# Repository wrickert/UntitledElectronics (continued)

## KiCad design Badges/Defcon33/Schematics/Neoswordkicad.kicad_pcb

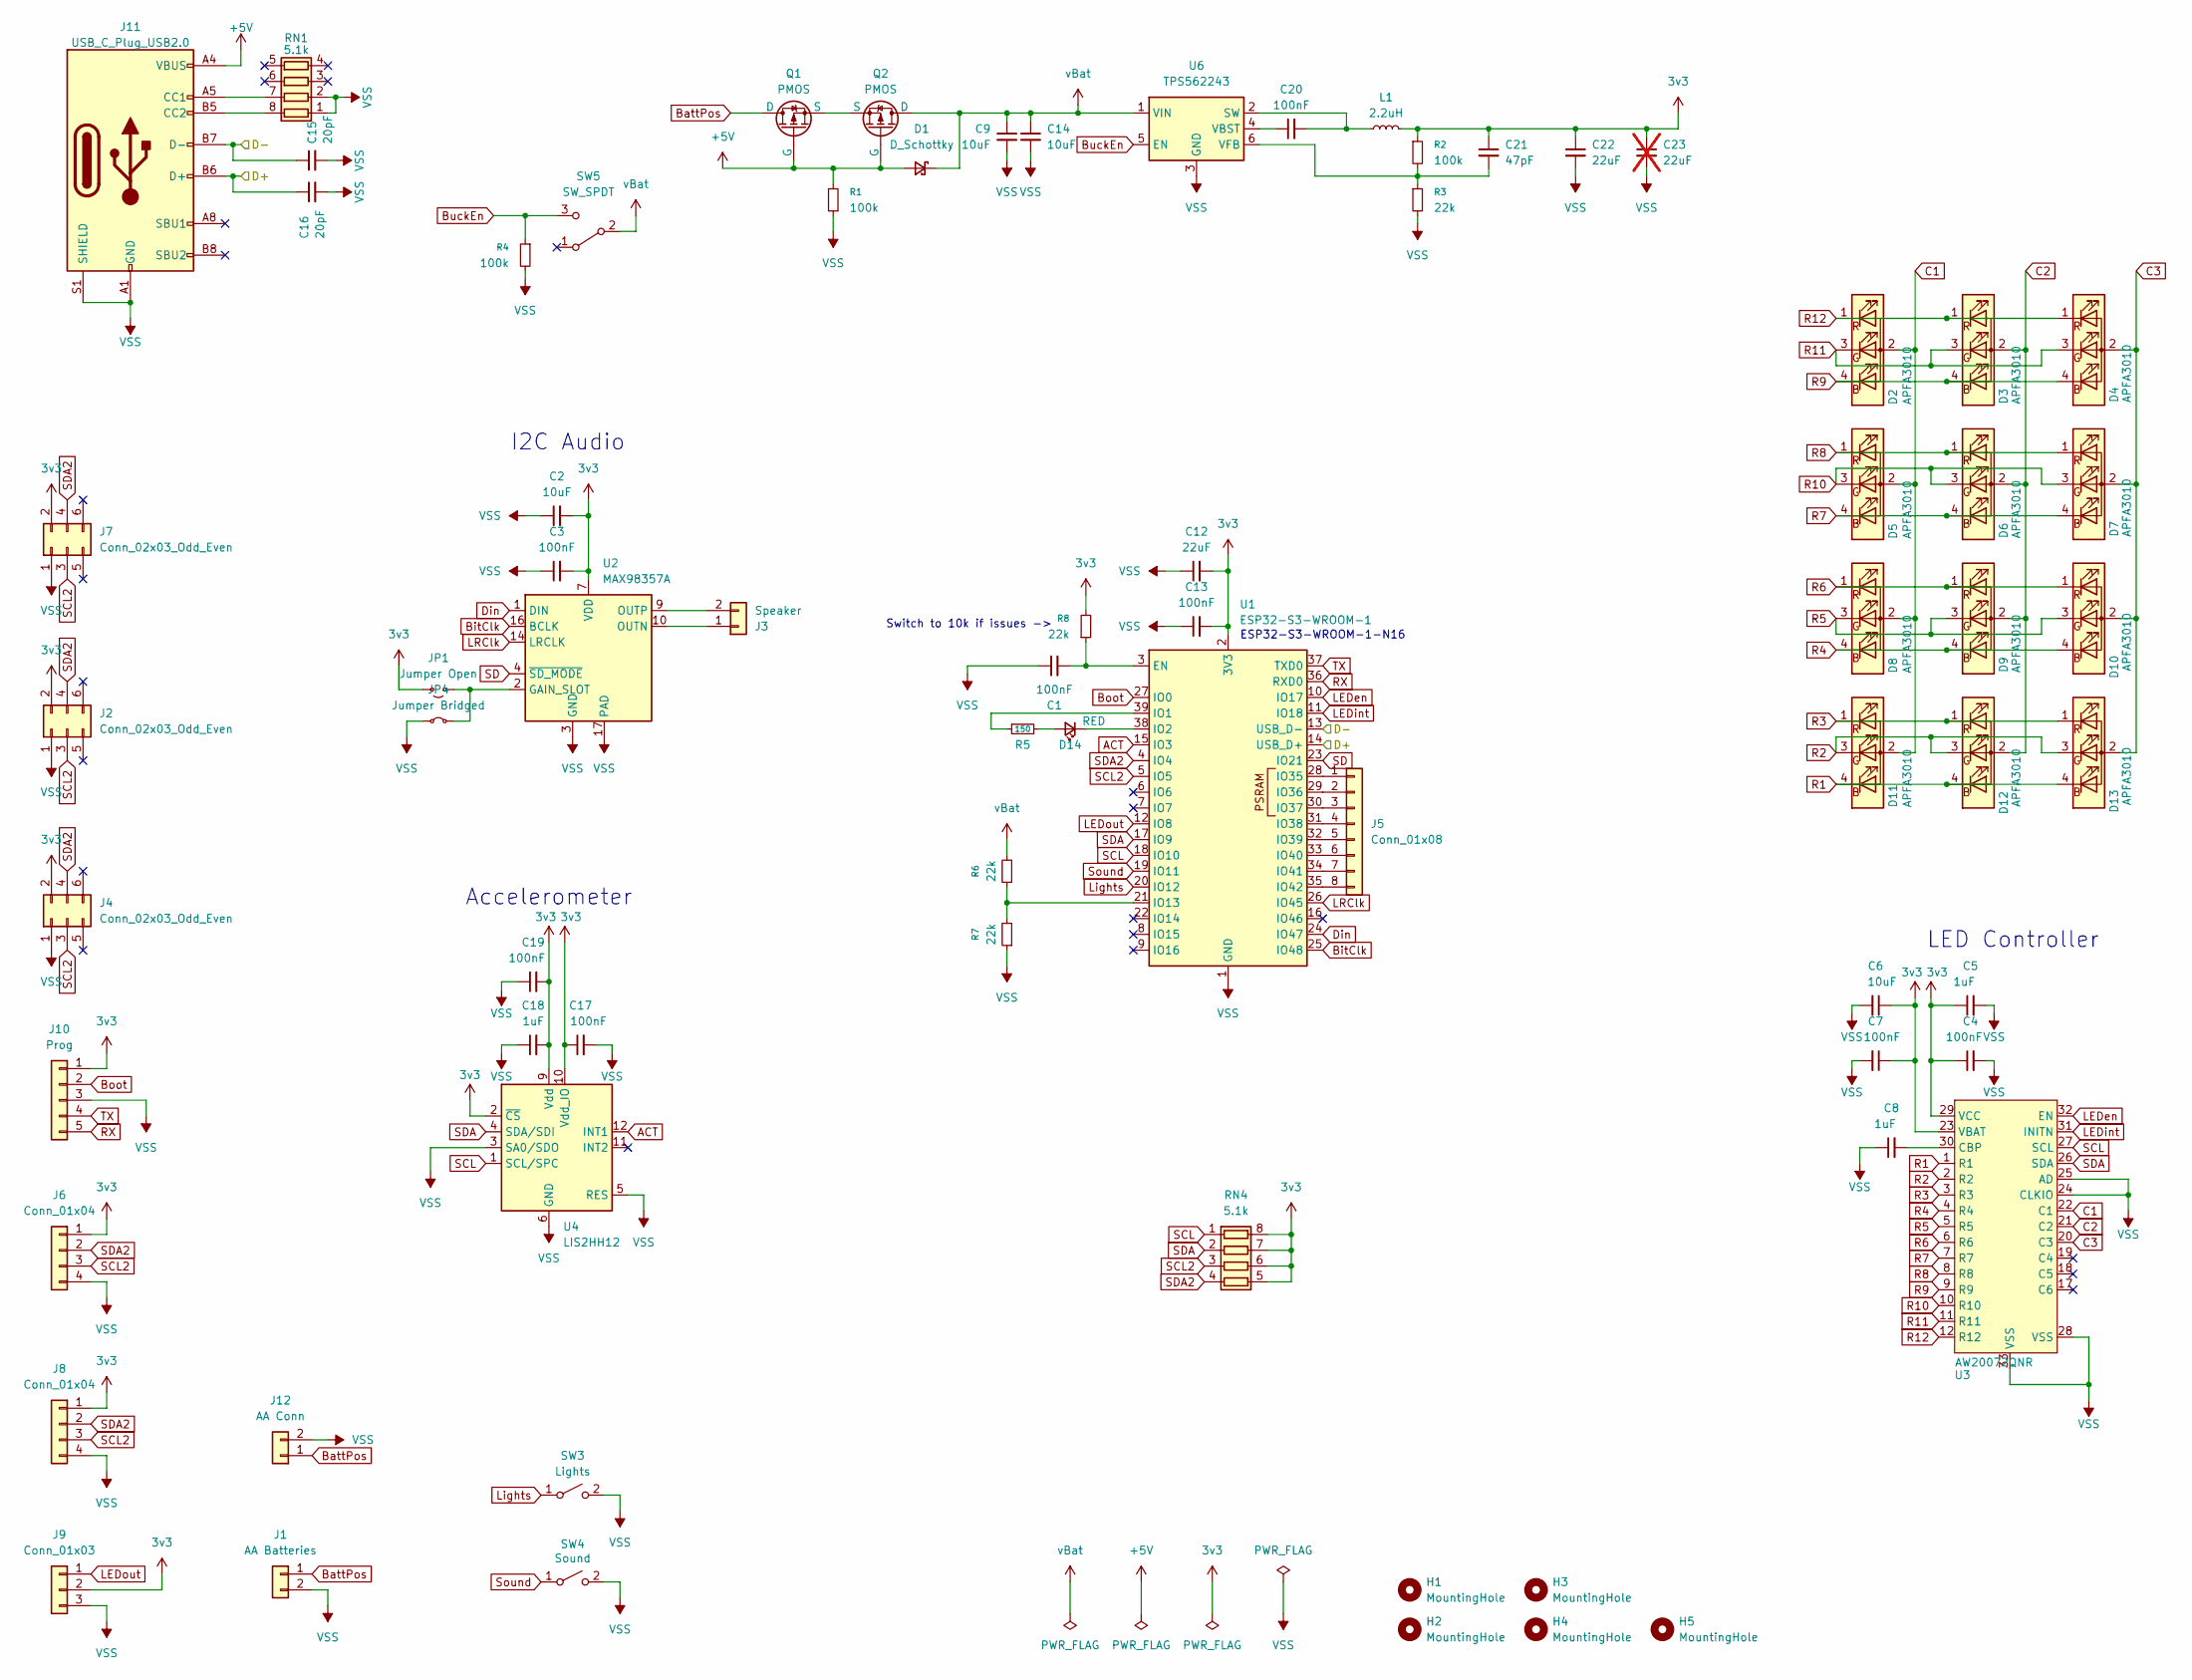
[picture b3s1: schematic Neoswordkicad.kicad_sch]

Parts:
C1, C3, C4, C7, C13, C17, C19, C20: 100nF; C_0805_2012Metric
C2, C6, C9, C14: 10uF; C_0805_2012Metric
C5, C8, C18: 1uF; C_0805_2012Metric
C12, C22: 22uF; C_0805_2012Metric
C15, C16: 20pF; C_0805_2012Metric
C21: 47pF; C_0805_2012Metric
C23: 22uF; C_0805_2012Metric; not fitted
D1: D_Schottky; D_0805_2012Metric
D2, D3, D4, D5, D6, D7, D8, D9, D10, D11, D12, D13: APFA3010; FM-3510RGBA-SG_RGB
D14: RED
H1, H2: MountingHole; MountingHole_3.2mm_M3_DIN965_Pad
H3: MountingHole; MountingHole_3.2mm_M3
H4, H5: MountingHole; Threaded_Standoffs
J1: AA Batteries; 1016_2AA
J2, J4, J7: Conn_02x03_Odd_Even; PinHeader_2x03_P2.54mm_Vertical
J3: Speaker; Molex_PicoBlade_53261-0271_1x02-1MP_P1.25mm_Horizontal
J5: Conn_01x08; PinHeader_1x08_P1.00mm_Vertical
J6, J8: Conn_01x04; Molex_PicoBlade_53261-0471_1x04-1MP_P1.25mm_Horizontal
J9: Conn_01x03; PinHeader_1x03_P2.54mm_Vertical
J10: Prog; PinHeader_1x05_P2.54mm_Vertical
J11: USB_C_Plug_USB2.0; USB_C_Receptical-Jing
J12: AA Conn; Molex_PicoBlade_53261-0271_1x02-1MP_P1.25mm_Horizontal
JP1: Jumper Open; SolderJumper-2_P1.3mm_Open_TrianglePad1.0x1.5mm
JP4: Jumper Bridged; SolderJumper-2_P1.3mm_Bridged_RoundedPad1.0x1.5mm
L1: 2.2uH; L_Vishay_IFSC-1515AH_4x4x1.8mm
Q1, Q2: PMOS; SOT-23
R1, R2, R4: 100k; R_0805_2012Metric
R3, R6, R7, R8: 22k; R_0805_2012Metric
R5: 150; R_0805_2012Metric
RN1, RN4: 5.1k; R_Array_Convex_4x0603
SW3: Lights; TS3315A
SW4: Sound; TS3315A
SW5: SW_SPDT; SK-3296S_switch
U1: ESP32-S3-WROOM-1
U2: MAX98357A; TQFN-16-1EP_3x3mm_P0.5mm_EP1.23x1.23mm
U3: AW20072QNR; QFN-32-1EP_4x4mm_P0.4mm_EP2.9x2.9mm
U4: LIS2HH12; LGA-12_2x2mm_P0.5mm
U6: TPS562243; SOT-563

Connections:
3v3: C2.2, C3.2, C4.1, C5.1, C6.1, C7.1, C12.2, C13.2, C17.1, C18.2, C19.2, C21.1, C22.1, C23.1, J2.2, J4.2, J6.1, J7.2, J8.1, J9.2, J10.1, JP1.2 (B), L1.2, R2.1, R8.2, RN4.5 (R4.2), RN4.6 (R3.2), RN4.7 (R2.2), RN4.8 (R1.2), U1.2 (3V3), U2.7 (VDD), U2.8 (VDD), U3.13 (VBAT), U3.23 (VBAT), U3.29 (VCC), U4.2 (~CS), U4.9 (Vdd), U4.10 (Vdd_IO)
+5V: D1.2 (A), J11.A4 (VBUS), J11.A9 (VBUS), J11.B4 (VBUS), J11.B9 (VBUS), Q1.1 (G), Q2.1 (G), R1.1
/D+: C16.1, J11.A6 (D+), J11.B6 (D+), U1.14 (USB_D+)
/D-: C15.1, J11.A7 (D-), J11.B7 (D-), U1.13 (USB_D-)
ACT: U1.15 (IO3), U4.12 (INT1)
BattPos: J1.1, J12.1, Q1.3 (D)
BitClk: U1.25 (IO48), U2.16 (BCLK)
Boot: J10.2, U1.27 (IO0)
BuckEn: R4.1, SW5.3 (C), U6.5 (EN)
C1: D2.2 (A), D5.2 (A), D8.2 (A), D11.2 (A), U3.22 (C1)
C2: D3.2 (A), D6.2 (A), D9.2 (A), D12.2 (A), U3.21 (C2)
C3: D4.2 (A), D7.2 (A), D10.2 (A), D13.2 (A), U3.20 (C3)
Din: U1.24 (IO47), U2.1 (DIN)
LEDen: U1.10 (IO17), U3.32 (EN)
LEDint: U1.11 (IO18), U3.31 (INITN)
LEDout: J9.1, U1.12 (IO8)
LRClk: U1.26 (IO45), U2.14 (LRCLK)
Lights: SW3.1 (A), U1.20 (IO12)
unnamed: D14.2 (A), R5.2
unnamed: D14.1 (K), U1.38 (IO2)
unnamed: J3.1, U2.10 (OUTN)
unnamed: J3.2, U2.9 (OUTP)
unnamed: J5.1, U1.28 (IO35)
unnamed: J5.2, U1.29 (IO36)
unnamed: J5.3, U1.30 (IO37)
unnamed: J5.4, U1.31 (IO38)
unnamed: J5.5, U1.32 (IO39)
unnamed: J5.6, U1.33 (IO40)
unnamed: J5.7, U1.34 (IO41)
unnamed: J5.8, U1.35 (IO42)
unnamed: J11.A5 (CC1), RN1.7 (R2.2)
unnamed: J11.B5 (CC2), RN1.8 (R1.2)
unnamed: JP1.1 (A), JP4.2 (B), U2.2 (GAIN_SLOT)
unnamed: Q1.2 (S), Q2.2 (S)
unnamed: C1.2, R8.1, U1.3 (EN)
unnamed: R5.1, U1.39 (IO1)
unnamed: R6.1, R7.2, U1.21 (IO13)
unnamed: C8.2, U3.30 (CBP)
unnamed: C20.2, L1.1, U6.2 (SW)
unnamed: C20.1, U6.4 (VBST)
unnamed: C21.2, R2.2, R3.1, U6.6 (VFB)
R1: D11.4 (B), D12.4 (B), D13.4 (B), U3.1 (R1)
R2: D11.3 (G), D12.3 (G), D13.3 (G), U3.2 (R2)
R3: D11.1 (R), D12.1 (R), D13.1 (R), U3.3 (R3)
R4: D8.4 (B), D9.4 (B), D10.4 (B), U3.4 (R4)
R5: D8.3 (G), D9.3 (G), D10.3 (G), U3.5 (R5)
R6: D8.1 (R), D9.1 (R), D10.1 (R), U3.6 (R6)
R7: D5.4 (B), D6.4 (B), D7.4 (B), U3.7 (R7)
R8: D5.1 (R), D6.1 (R), D7.1 (R), U3.8 (R8)
R9: D2.4 (B), D3.4 (B), D4.4 (B), U3.9 (R9)
R10: D5.3 (G), D6.3 (G), D7.3 (G), U3.10 (R10)
R11: D2.3 (G), D3.3 (G), D4.3 (G), U3.11 (R11)
R12: D2.1 (R), D3.1 (R), D4.1 (R), U3.12 (R12)
RX: J10.5, U1.36 (RXD0)
SCL: RN4.1 (R1.1), U1.18 (IO10), U3.27 (SCL), U4.1 (SCL/SPC)
SCL2: J2.3, J4.3, J6.3, J7.3, J8.3, RN4.3 (R3.1), U1.5 (IO5)
SD: U1.23 (IO21), U2.4 (~SD_MODE)
SDA: RN4.2 (R2.1), U1.17 (IO9), U3.26 (SDA), U4.4 (SDA/SDI)
SDA2: J2.4, J4.4, J6.2, J7.4, J8.2, RN4.4 (R4.1), U1.4 (IO4)
Sound: SW4.1 (A), U1.19 (IO11)
TX: J10.4, U1.37 (TXD0)
VSS: C1.1, C2.1, C3.1, C4.2, C5.2, C6.2, C7.2, C8.1, C9.2, C12.1, C13.1, C14.2, C15.2, C16.2, C17.2, C18.1, C19.1, C22.2, C23.2, J1.2, J2.1, J4.1, J6.4, J7.1, J8.4, J9.3, J10.3, J11.A1 (GND), J11.A12 (GND), J11.B1 (GND), J11.B12 (GND), J11.S1 (SHIELD), J12.2, JP4.1 (A), R1.2, R3.2, R4.2, R7.1, RN1.1 (R1.1), RN1.2 (R2.1), SW3.2 (B), SW4.2 (B), U1.1 (GND), U1.40 (GND), U1.41 (GND), U2.3 (GND), U2.11 (GND), U2.15 (GND), U2.17 (PAD), U3.24 (CLKIO), U3.25 (AD), U3.28 (VSS), U3.33 (VSS), U4.3 (SA0/SDO), U4.5 (RES), U4.6 (GND), U4.7 (GND), U4.8 (GND), U6.3 (GND)
vBat: C9.1, C14.1, D1.1 (K), Q2.3 (D), R6.2, SW5.2 (B), U6.1 (VIN)

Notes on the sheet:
ESP32-S3-WROOM-1-N16
Accelerometer
LED Controller
Switch to 10k if issues ->
I2C Audio

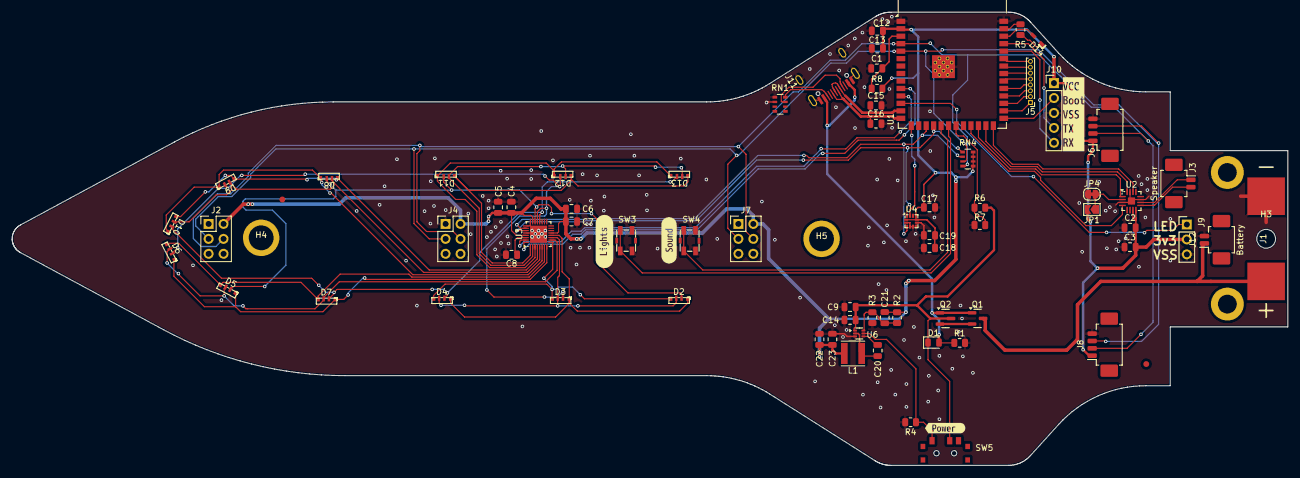
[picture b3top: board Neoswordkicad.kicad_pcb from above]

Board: 2 copper layers, 217.0 x 77.1 mm, 79 parts (0 on the bottom side), 63 nets.

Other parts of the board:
kibuzzard-684F57A2: G***; kibuzzard-684F57A2
kibuzzard-684F57B2: G***; kibuzzard-684F57B2
kibuzzard-684F5906: G***; kibuzzard-684F5906
kibuzzard-6850B9A9: G***; kibuzzard-6850B9A9

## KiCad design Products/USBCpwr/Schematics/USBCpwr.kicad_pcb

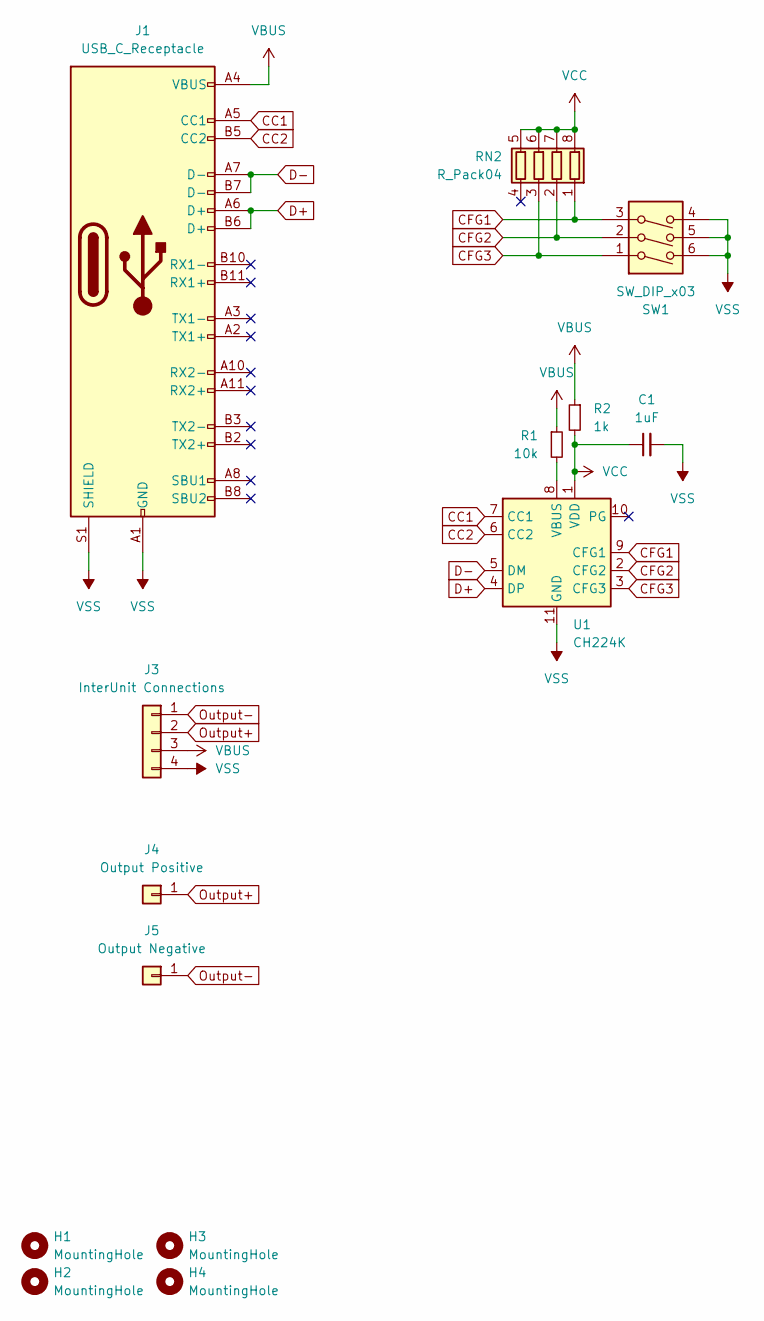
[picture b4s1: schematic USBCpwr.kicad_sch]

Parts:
C1: 1uF; C_0805_2012Metric
H1, H2, H3, H4: MountingHole; MountingHole_2.2mm_M2
J1: USB_C_Receptacle; USB_C_Receptical-Jing
J3: InterUnit Connections; Altech_AK100_1x04_P5.00mm
J4: Output Positive; Banana24_245_1
J5: Output Negative; Banana24_245_1
R1: 10k; R_0805_2012Metric
R2: 1k; R_0805_2012Metric
RN2: R_Pack04; R_Array_Convex_4x0603
SW1: SW_DIP_x03; SW_DIP_SPSTx03_Slide_6.7x9.18mm_W6.73mm_P2.54mm_LowProfile_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
U1: CH224K; SSOP-10-1EP_3.9x4.9mm_P1mm_EP2.1x3.3mm

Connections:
CC1: J1.A5 (CC1), U1.7 (CC1)
CC2: J1.B5 (CC2), U1.6 (CC2)
CFG1: RN2.1 (R1.1), SW1.3, U1.9 (CFG1)
CFG2: RN2.2 (R2.1), SW1.2, U1.2 (CFG2)
CFG3: RN2.3 (R3.1), SW1.1, U1.3 (CFG3)
D+: J1.A6 (D+), J1.B6 (D+), U1.4 (DP)
D-: J1.A7 (D-), J1.B7 (D-), U1.5 (DM)
unnamed: R1.2, U1.8 (VBUS)
Output+: J3.2, J4.1
Output-: J3.1, J5.1
VBUS: J1.A4 (VBUS), J1.A9 (VBUS), J1.B4 (VBUS), J1.B9 (VBUS), J3.3, R1.1, R2.1
VCC: C1.1, R2.2, RN2.5 (R4.2), RN2.6 (R3.2), RN2.7 (R2.2), RN2.8 (R1.2), U1.1 (VDD)
VSS: C1.2, J1.A1 (GND), J1.A12 (GND), J1.B1 (GND), J1.B12 (GND), J1.S1 (SHIELD), J3.4, SW1.4, SW1.5, SW1.6, U1.11 (GND)

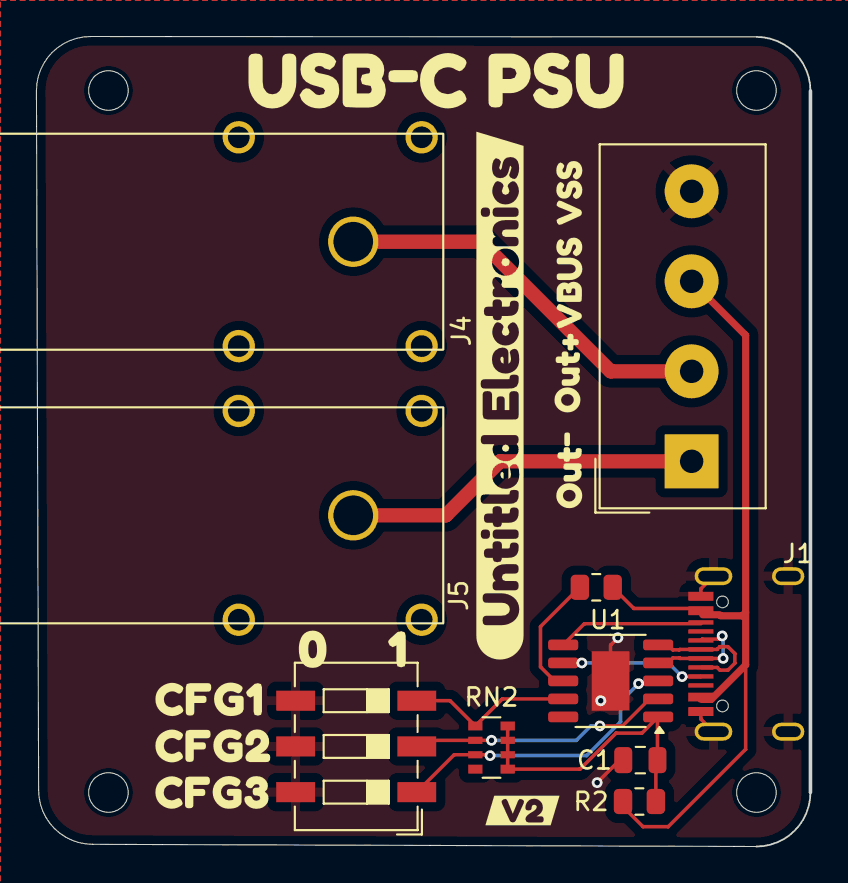
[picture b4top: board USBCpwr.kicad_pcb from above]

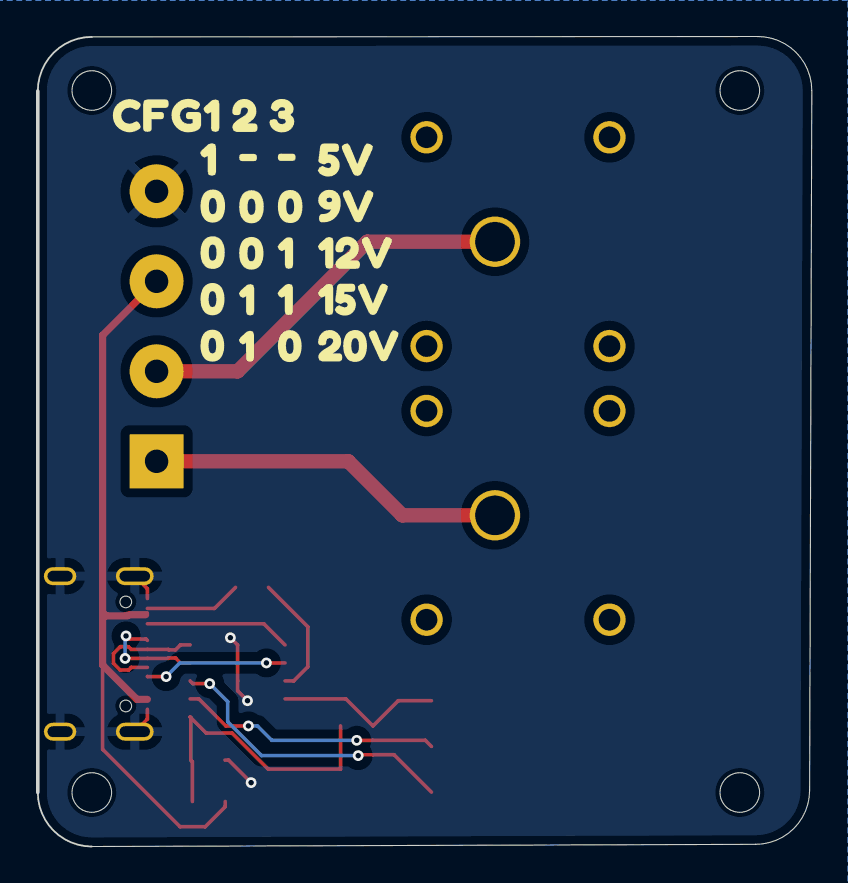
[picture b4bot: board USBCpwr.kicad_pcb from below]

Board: 2 copper layers, 42.9 x 44.9 mm, 28 parts (5 on the bottom side), 13 nets.

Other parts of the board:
kibuzzard-6903A84F: G***; kibuzzard-6903A84F
kibuzzard-67741D43: G***; kibuzzard-67741D43
kibuzzard-67742A98: G***; kibuzzard-67742A98
kibuzzard-67742AAA: G***; kibuzzard-67742AAA
kibuzzard-67742ABC: G***; kibuzzard-67742ABC
kibuzzard-67742BC8: G***; kibuzzard-67742BC8
kibuzzard-67742BCF: G***; kibuzzard-67742BCF
kibuzzard-67742BE6: G***; kibuzzard-67742BE6
kibuzzard-67742BF7: G***; kibuzzard-67742BF7
kibuzzard-67742CEC: G***; kibuzzard-67742CEC
kibuzzard-67742CFE: G***; kibuzzard-67742CFE
kibuzzard-6903877E: G***; kibuzzard-6903877E
kibuzzard-67742882: G***; kibuzzard-67742882
kibuzzard-67742999: G***; kibuzzard-67742999

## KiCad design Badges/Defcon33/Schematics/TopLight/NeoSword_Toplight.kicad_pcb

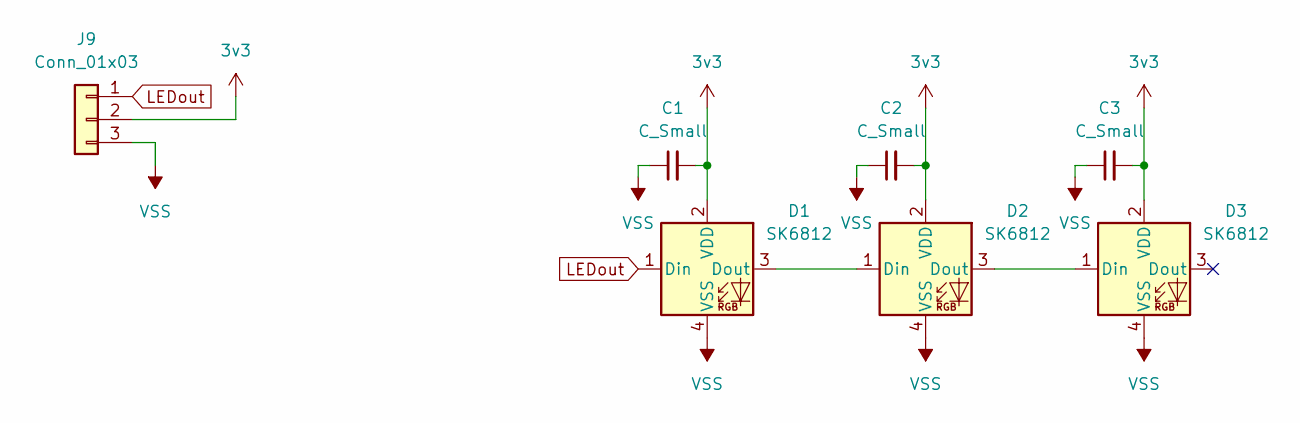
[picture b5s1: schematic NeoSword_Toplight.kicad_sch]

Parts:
C1, C2, C3: C_Small; C_0805_2012Metric
D1, D2, D3: SK6812; SK6812SIDE-A-RVS
J9: Conn_01x03; PinHeader_1x03_P2.54mm_Vertical_SMD_Pin1Left

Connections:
3v3: C1.2, C2.2, C3.2, D1.2 (VDD), D2.2 (VDD), D3.2 (VDD), J9.2
LEDout: D1.1 (Din), J9.1
unnamed: D1.3 (Dout), D2.1 (Din)
unnamed: D2.3 (Dout), D3.1 (Din)
VSS: C1.1, C2.1, C3.1, D1.4 (VSS), D2.4 (VSS), D3.4 (VSS), J9.3

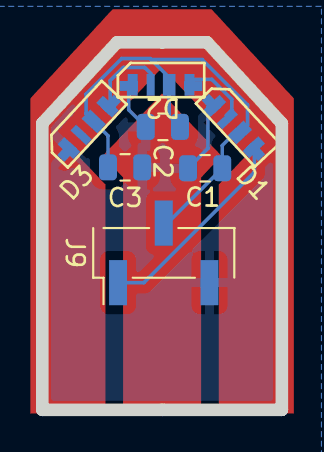
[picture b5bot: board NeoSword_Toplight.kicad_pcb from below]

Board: 2 copper layers, 13.3 x 20.4 mm, 7 parts (7 on the bottom side), 5 nets.

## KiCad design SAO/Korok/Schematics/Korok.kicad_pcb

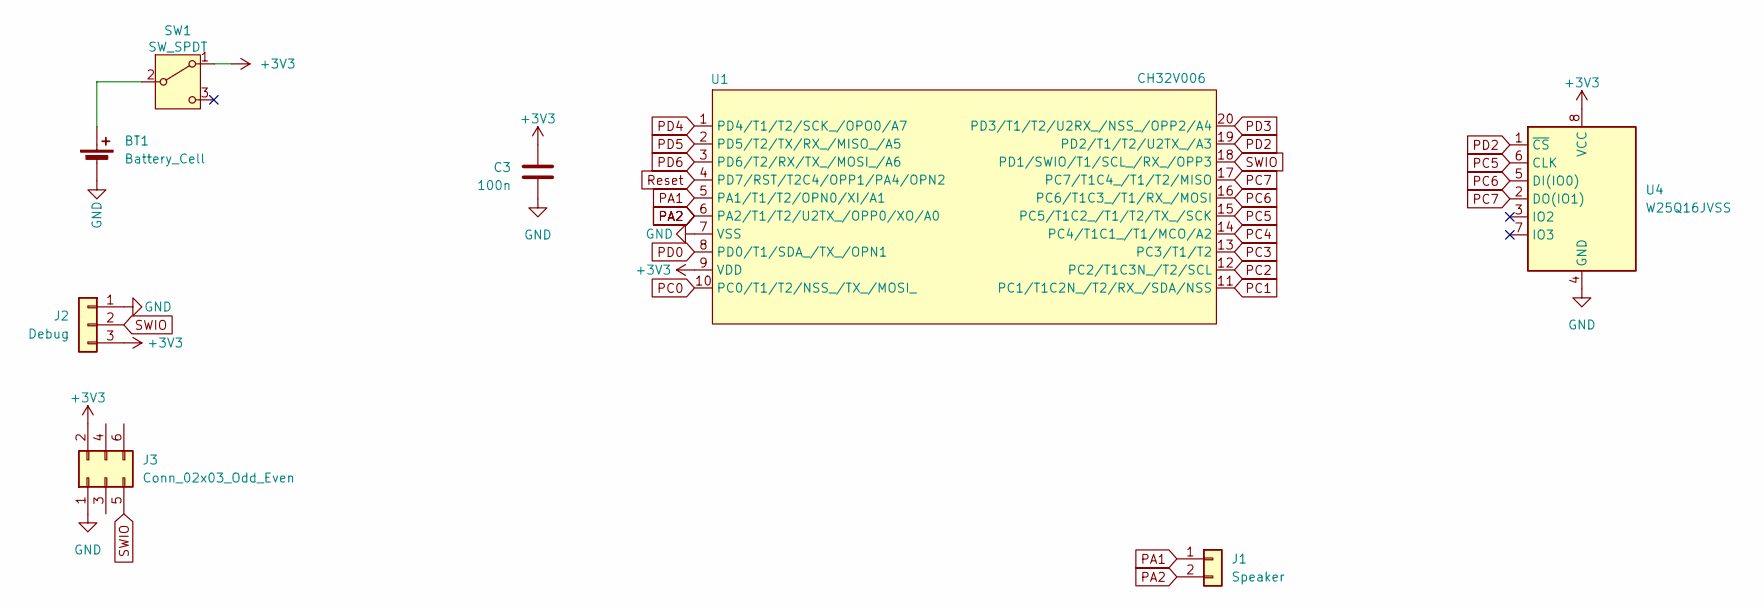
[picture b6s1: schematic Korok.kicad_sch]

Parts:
BT1: Battery_Cell; BatteryHolder_Keystone_3034_1x20mm
C3: 100n; C_0805_2012Metric
J1: Speaker; Fuet-1230
J2: Debug; PinSocket_1x03_P2.54mm_Vertical
J3: Conn_02x03_Odd_Even; PinHeader_2x03_P2.54mm_Vertical_SMD
SW1: SW_SPDT; SK-3296S_switch
U1: CH32V006; TSSOP-20_4.4x6.5mm_P0.65mm
U4: W25Q16JVSS; SSOP-8_3.95x5.21x3.27mm_P1.27mm

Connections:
+3V3: C3.1, J2.3, J3.2, SW1.1 (A), U1.9 (VDD), U4.8 (VCC)
GND: BT1.2 (-), C3.2, J2.1, J3.1, U1.7 (VSS), U4.4 (GND)
unnamed: BT1.1 (+), SW1.2 (B)
PA1: J1.1, U1.5 (PA1/T1/T2/OPN0/XI/A1)
PA2: J1.2, U1.6 (PA2/T1/T2/U2TX_/OPP0/XO/A0)
PC0: U1.10 (PC0/T1/T2/NSS_/TX_/MOSI_)
PC1: U1.11 (PC1/T1C2N_/T2/RX_/SDA/NSS)
PC2: U1.12 (PC2/T1C3N_/T2/SCL)
PC3: U1.13 (PC3/T1/T2)
PC4: U1.14 (PC4/T1C1_/T1/MCO/A2)
PC5: U1.15 (PC5/T1C2_/T1/T2/TX_/SCK), U4.6 (CLK)
PC6: U1.16 (PC6/T1C3_/T1/RX_/MOSI), U4.5 (DI(IO0))
PC7: U1.17 (PC7/T1C4_/T1/T2/MISO), U4.2 (DO(IO1))
PD0: U1.8 (PD0/T1/SDA_/TX_/OPN1)
PD2: U1.19 (PD2/T1/T2/U2TX_/A3), U4.1 (~CS)
PD3: U1.20 (PD3/T1/T2/U2RX_/NSS_/OPP2/A4)
PD4: U1.1 (PD4/T1/T2/SCK_/OPO0/A7)
PD5: U1.2 (PD5/T2/TX/RX_/MISO_/A5)
PD6: U1.3 (PD6/T2/RX/TX_/MOSI_/A6)
Reset: U1.4 (PD7/RST/T2C4/OPP1/PA4/OPN2)
SWIO: J2.2, J3.5, U1.18 (PD1/SWIO/T1/SCL_/RX_/OPP3)

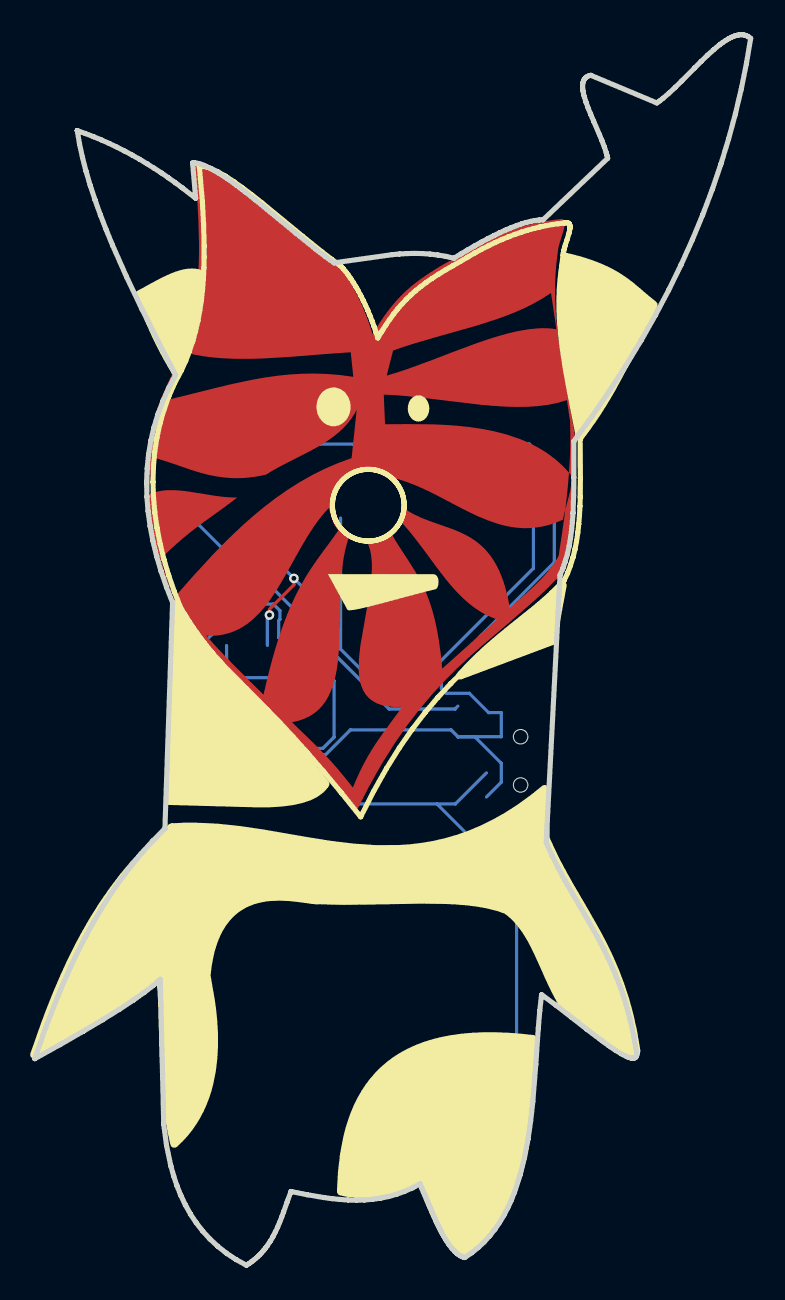
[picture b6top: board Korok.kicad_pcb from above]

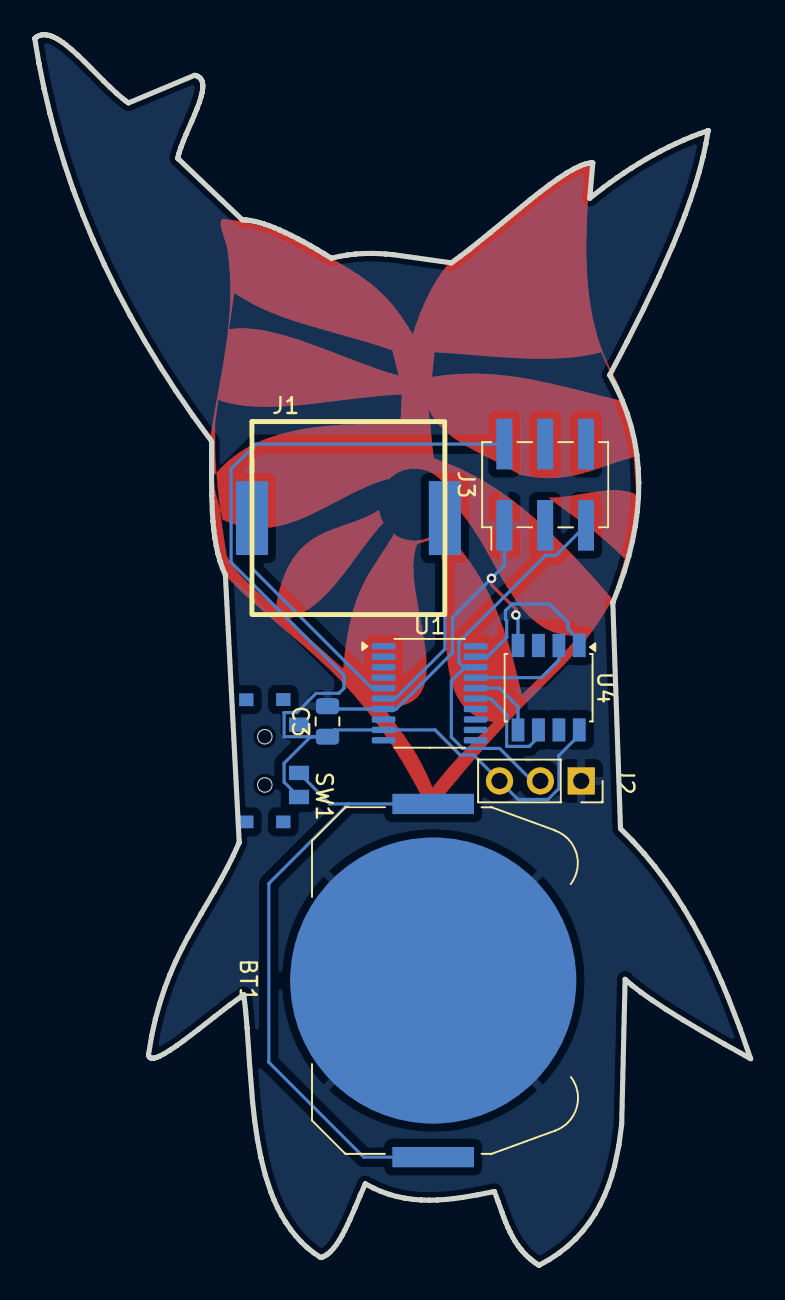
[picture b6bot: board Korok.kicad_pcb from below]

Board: 2 copper layers, 44.5 x 76.5 mm, 8 parts (8 on the bottom side), 10 nets.

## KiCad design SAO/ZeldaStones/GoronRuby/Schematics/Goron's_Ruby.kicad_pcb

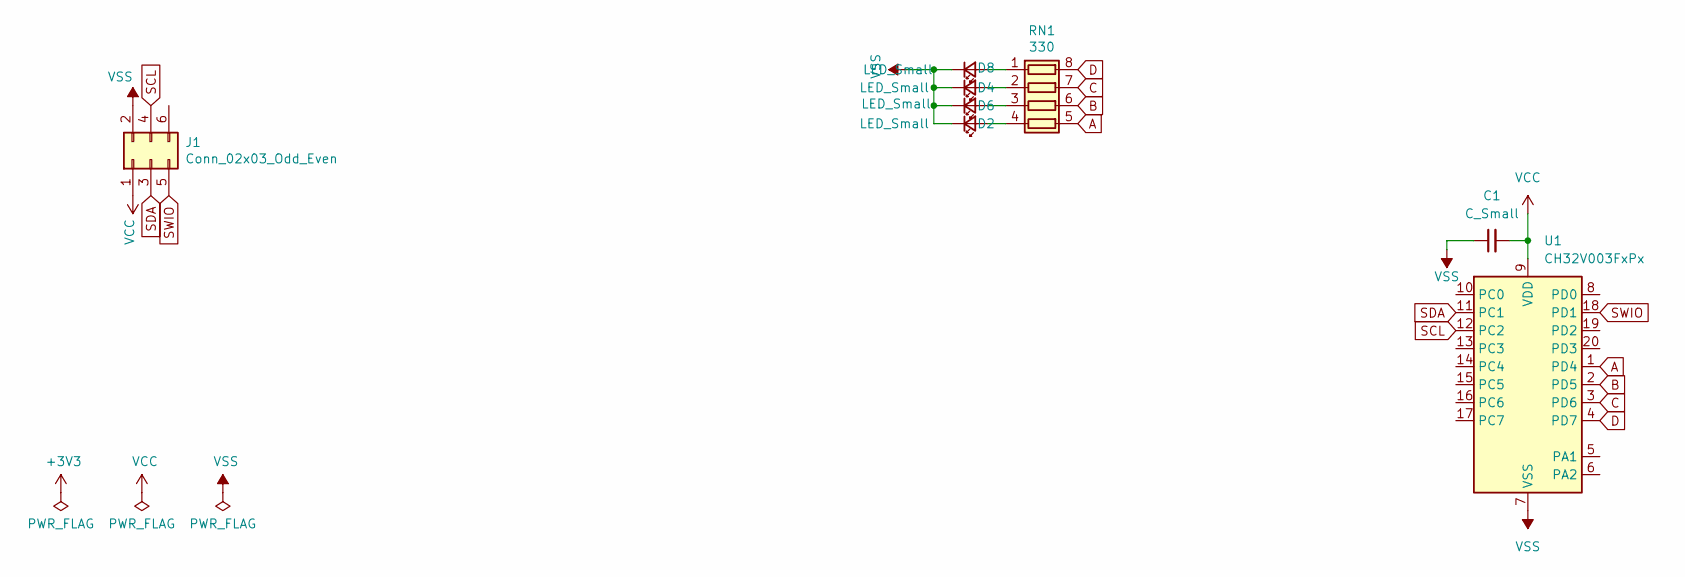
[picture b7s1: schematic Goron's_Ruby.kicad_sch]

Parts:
C1: C_Small; C_0805_2012Metric
D2, D4, D6, D8: LED_Small; LED_0603_1608Metric
J1: Conn_02x03_Odd_Even; PinHeader_2x03_P2.54mm_Vertical_SMD
RN1: 330; R_Array_Convex_4x0603
U1: CH32V003FxPx; TSSOP-20_4.4x6.5mm_P0.65mm

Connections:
A: RN1.5 (R4.2), U1.1 (PD4)
B: RN1.6 (R3.2), U1.2 (PD5)
C: RN1.7 (R2.2), U1.3 (PD6)
D: RN1.8 (R1.2), U1.4 (PD7)
unnamed: D2.2 (A), RN1.4 (R4.1)
unnamed: D4.2 (A), RN1.2 (R2.1)
unnamed: D6.2 (A), RN1.3 (R3.1)
unnamed: D8.2 (A), RN1.1 (R1.1)
SCL: J1.4, U1.12 (PC2)
SDA: J1.3, U1.11 (PC1)
SWIO: J1.5, U1.18 (PD1)
VCC: C1.2, J1.1, U1.9 (VDD)
VSS: C1.1, D2.1 (K), D4.1 (K), D6.1 (K), D8.1 (K), J1.2, U1.7 (VSS)

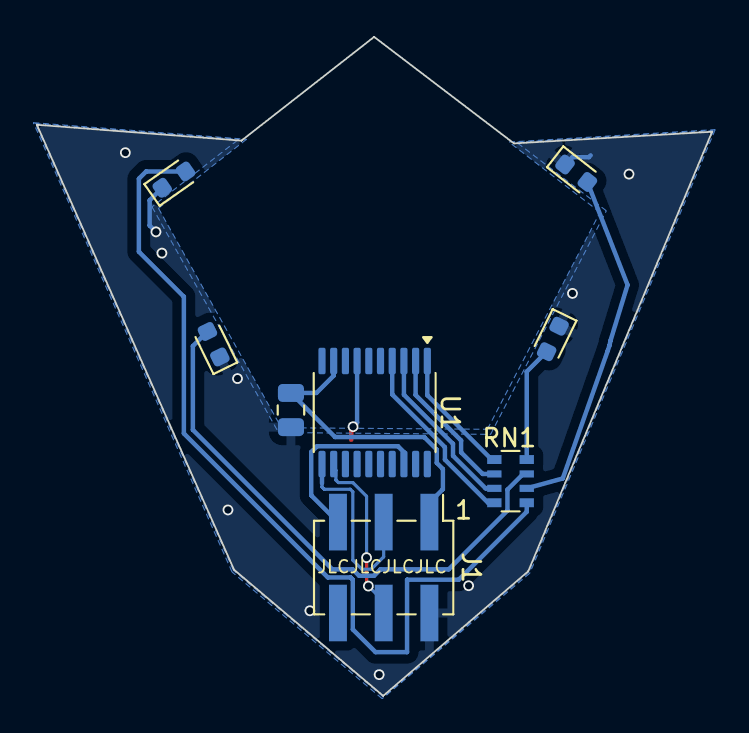
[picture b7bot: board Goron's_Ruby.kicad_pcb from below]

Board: 2 copper layers, 37.5 x 36.6 mm, 8 parts (8 on the bottom side), 13 nets.

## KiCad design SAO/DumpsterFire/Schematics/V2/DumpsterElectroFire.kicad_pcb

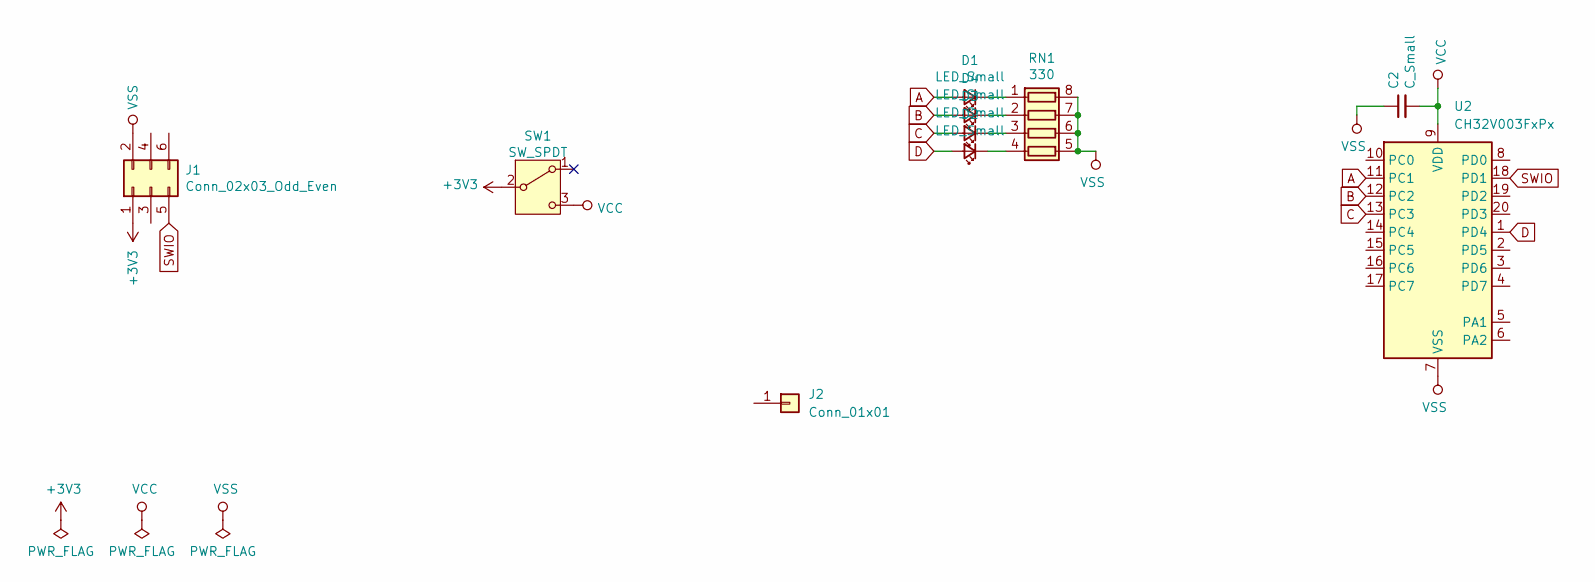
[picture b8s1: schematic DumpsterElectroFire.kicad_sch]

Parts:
C2: C_Small; C_0805_2012Metric
D1, D2, D3, D4: LED_Small; LED_0603_1608Metric
J1: Conn_02x03_Odd_Even; PinHeader_2x03_P2.54mm_Vertical_SMD
J2: Conn_01x01; TestPoint_5016
RN1: 330; R_Array_Convex_4x0603
SW1: SW_SPDT; SK-3296S_switch
U2: CH32V003FxPx; TSSOP-20_4.4x6.5mm_P0.65mm

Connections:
+3V3: J1.1, SW1.2 (B)
A: D1.2 (A), U2.11 (PC1)
B: D4.2 (A), U2.12 (PC2)
C: D3.2 (A), U2.13 (PC3)
D: D2.2 (A), U2.1 (PD4)
unnamed: D1.1 (K), RN1.1 (R1.1)
unnamed: D2.1 (K), RN1.4 (R4.1)
unnamed: D3.1 (K), RN1.3 (R3.1)
unnamed: D4.1 (K), RN1.2 (R2.1)
SWIO: J1.5, U2.18 (PD1)
VCC: C2.2, SW1.3 (C), U2.9 (VDD)
VSS: C2.1, J1.2, RN1.5 (R4.2), RN1.6 (R3.2), RN1.7 (R2.2), RN1.8 (R1.2), U2.7 (VSS)

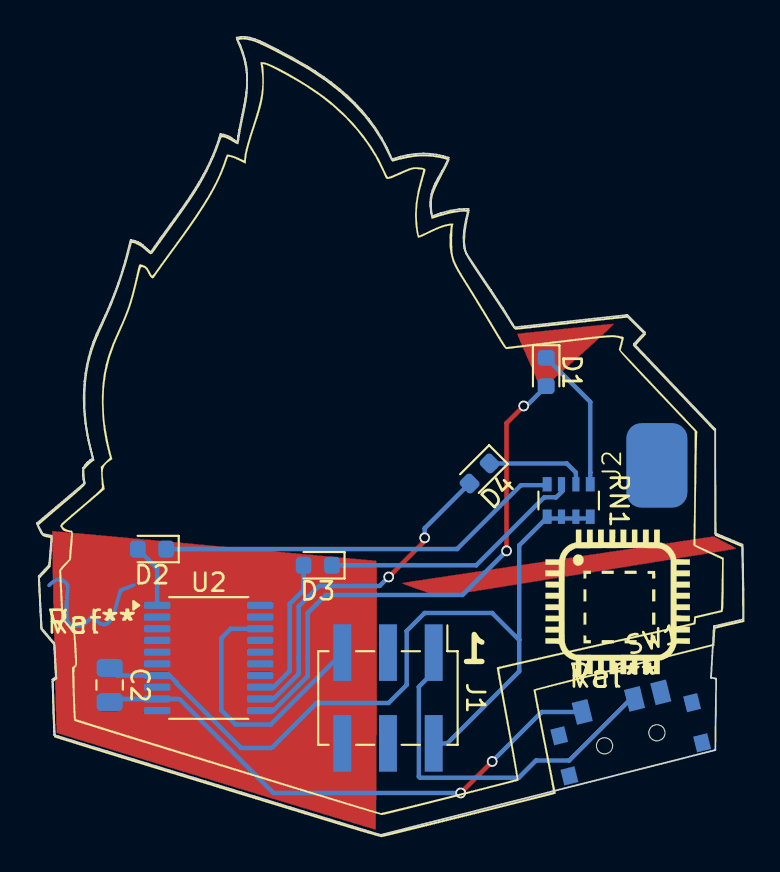
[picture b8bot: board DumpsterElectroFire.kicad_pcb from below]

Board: 2 copper layers, 39.2 x 44.3 mm, 13 parts (12 on the bottom side), 12 nets.

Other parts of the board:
Ref**: Val**; dumpsterFireMiddle
Ref**#2: Val**; W
Ref**#3: Val**; UELogoVsmall

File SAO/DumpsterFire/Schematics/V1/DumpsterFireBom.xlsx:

Comment | Designator | Footprint | LCSC Part #（optional）
Side View LED | D1,D2,D3,D4 | 603 | C125114
Resistor Network | RN1 | 0603x4 | C149867
SPDT | SW1 | SW_SPDT | C128955
Pin Header | J1 | PinHeader_2x03_P2.54mm_Vertical_SMD | C77761

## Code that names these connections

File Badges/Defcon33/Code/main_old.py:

# main.py

from machine import I2C, Pin, I2S
from lis2hh12 import LIS2HH12
import time
import array
import ustruct
import math
import random

# I2S Config (update id and pins if needed for your board)
i2s = I2S(
    0,                          # I2S peripheral id (try 0 or 1)
    sck=Pin(48),                # Bit clock (BCLK)
    ws=Pin(45),                 # Word select (LRCLK)
    sd=Pin(47),                 # Serial data (DIN)
    mode=I2S.TX,
    bits=16,
    format=I2S.MONO,            # or I2S.STEREO if needed
    rate=8000, #22050,smaller file size       Audio sample rate
    ibuf=20000                  # Internal buffer length
)

# Setup I2C
i2c = I2C(0, scl=Pin(10), sda=Pin(9), freq=100000)
AW_ADDR = 0x3A

# Setup Pins
gpio17 = Pin(17, Pin.OUT)
lights = Pin(12, Pin.IN, Pin.PULL_UP)
audioEN = Pin(21, Pin.OUT)

# Sensitivity threshold (tweak this!)
SWING_THRESHOLD = 19  # In g's. Try 2-4, adjust as needed

# --- Basic read/write helpers for the aw20072 ---
def aw_write(reg, data):
    i2c.writeto_mem(AW_ADDR, reg, bytes([data]))

def aw_read(reg):
    return i2c.readfrom_mem(AW_ADDR, reg, 1)[0]

acc = LIS2HH12(i2c)


def aw20072_init():
    # Page 0
    aw_write(0xF0, 0xC0)
    aw_write(0x02, 0x01)  # software reset
    time.sleep(0.002)
    aw_write(0x03, 0x18)  # Imax, ALLON = 0
    aw_write(0x80, 0x02)  # SIZE config
    aw_write(0x01, 0x00)  # enter active mode

def aw20x_MaxOn():
    # Page 1 - set all color values to 0x3F
    aw_write(0xF0, 0xC1)
    for i in range(0x24):
        aw_write(i, 0x3F)

    # Page 2 - brightness registers (0xFF full)
    aw_write(0xF0, 0xC2)
    for i in range(0x24):
        aw_write(i, 0xFF)

def aw20x_Off():
    # Page 1 - set all color values to 0x3F
    aw_write(0xF0, 0xC1)
    for i in range(0x24):
        aw_write(i, 0x3F)

    # Page 2 - brightness registers (0xFF full)
    aw_write(0xF0, 0xC2)
    for i in range(0x24):
        aw_write(i, 0x00)

def playAudio(num):
    print("Playing Mombo number " + str(num))
    if num == 1:
        play = "tada.wav"
    elif num == 2:
        play = "Swing1.wav"
    elif num == 3:
        play = "Swing2.wav"
    elif num == 4:
        play = "Swing3.wav"
    elif num == 5:
        play = "listen.wav"

    with open(play, "rb") as f:
        f.read(44)  # Skip header
        while True:
            data = f.read(1024)
            if not data:
                break
            i2s.write(data)



def main():
    audioEN.on()
    time.sleep(0.01)

    playAudio(5)


    gpio17.on()   
    lights_state = 0
    # Your main code here
    print("Hello, MicroPython!")
    aw20072_init()
    while True:
        if not lights.value():  # Button pressed (active LOW)
            lights_state = not lights_state
            if lights_state:
                aw20x_MaxOn()
            else:
                aw20x_Off()
        # Debounce: wait for button release
            while not lights.value():
                time.sleep(0.01)
        time.sleep(0.01)

        x = acc.acceleration[0]
        y = acc.acceleration[1]
        z = acc.acceleration[2]

        # Calculate magnitude of acceleration vector
        magnitude = math.sqrt(x*x + y*y + z*z)

        print("Magnitude is " + str(magnitude))

        if magnitude > SWING_THRESHOLD:
            print("Found Swing")
            playAudio(random.randint(2,3))
            time.sleep(0.5)
            


if __name__ == "__main__":
    main()

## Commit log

2023-03-23 Adding Red Village Badge
2023-03-27 Created schematic and started firmware
2023-03-29 Changed RedVillage to ESP32-S2
2023-03-29 Pins
2023-04-06 Further updates
2023-04-07 Routing update
2023-04-14 V1 complete
2023-04-15 Added assembly notes
2023-05-16 V2 complete, Production quantity ordered
2023-05-21 Panelize-me!
2023-06-22 spring cleaning
2023-07-02 LVGL works
2023-07-03 Pulled apart
2023-07-09 Display Progress! TFT_eSPI FTW
2023-08-01 90 done
2023-08-04 Wahoo
2023-08-06 Only boss to go
2023-08-07 Firmware
2023-08-07 Firmware ready
2023-08-07 Ready for showtime
2023-08-14 Defcon Complete. Cleaned up repo and push
2024-03-29 Started CAD
2024-04-01 Trying a different latching Mechanism
2024-04-08 Moving
2024-04-08 Updates, ready for first print
2024-05-24 Started cybertastic
2024-05-31 CyberTastic schematic done
2024-05-31 Completed V1 Routing
2024-05-31 Moved gaussmouse and ordered V1
2024-06-25 I guess I'm going to defcon
2024-06-28 Ready to start PCB
2024-07-01 Some Schematic
2024-07-02 Layout complete
2024-07-14 Lets panel
2024-09-09 Started badge
2025-02-07 moar
2025-06-24 Fixing repo, adding SAOs
2025-06-25 Generated panel of stones
2025-06-26 Closer to sao
2025-07-07 OMG SUCH PRODUCTIVE
2025-07-23 Korok art
2025-07-23 Finished korok and toplight
2026-01-15 Progress on bsidesdsm
2026-02-13 Progress
2026-03-03 perhaps?
2026-03-27 Something something something git language
2026-04-01 Hard part done save
2026-04-01 ORDERED
2026-04-03 Code progress
2026-04-10 Lets build some boards
2026-05-07 PCBA
2026-05-11 ch585
2026-05-12 Probably the correct code this time
2026-06-02 almost cad
